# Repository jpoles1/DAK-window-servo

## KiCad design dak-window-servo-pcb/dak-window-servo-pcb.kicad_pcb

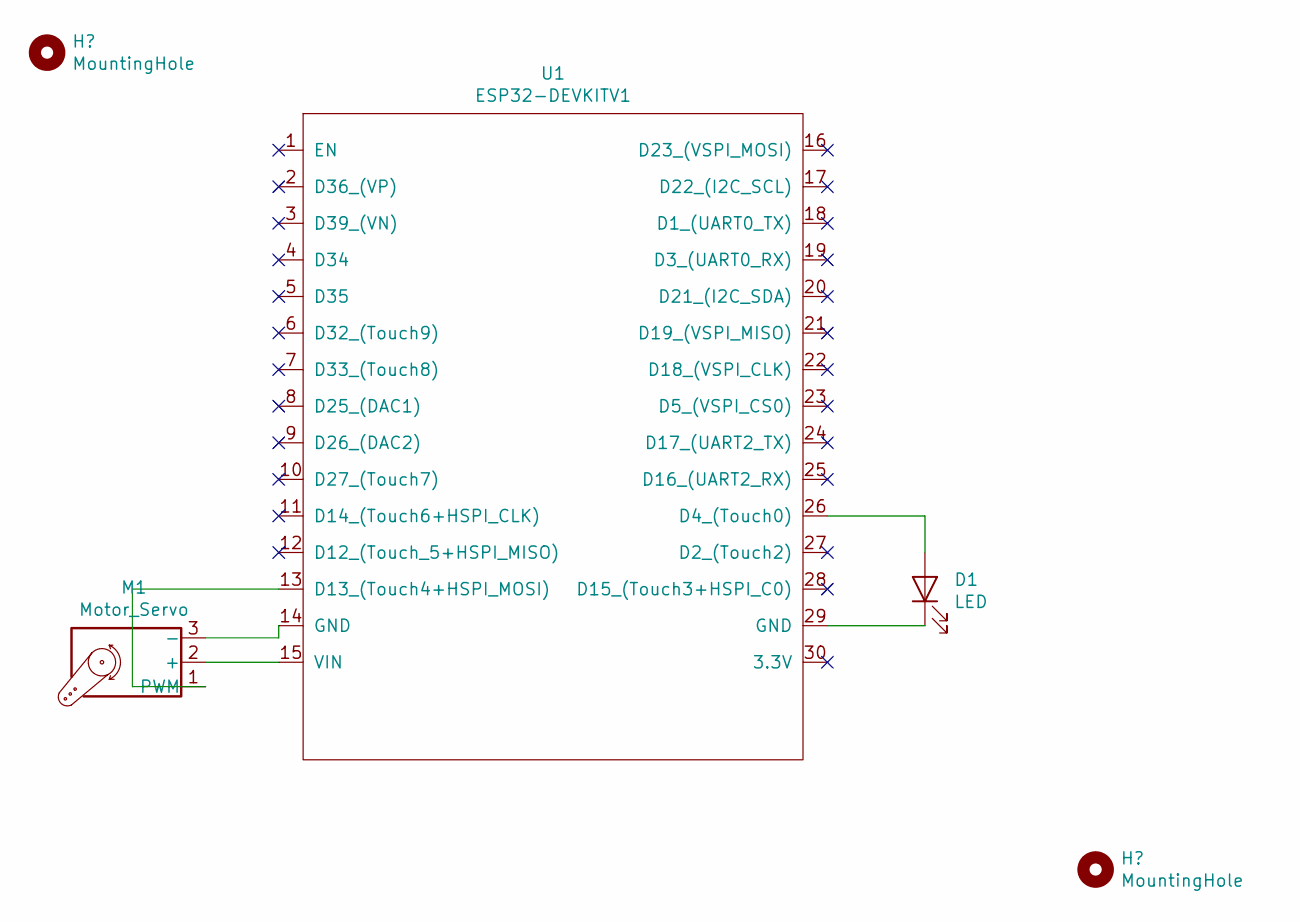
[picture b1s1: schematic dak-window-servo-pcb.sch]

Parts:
D1: LED; LED_D3.0mm
M1: Motor_Servo; Servo-Header
U1: ESP32-DEVKITV1

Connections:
unnamed: D1.1 (K), U1.29 (GND)
unnamed: D1.2 (A), U1.26 (D4_(Touch0))
unnamed: M1.1 (PWM), U1.13 (D13_(Touch4+HSPI_MOSI))
unnamed: M1.2 (+), U1.15 (VIN)
unnamed: M1.3 (-), U1.14 (GND)

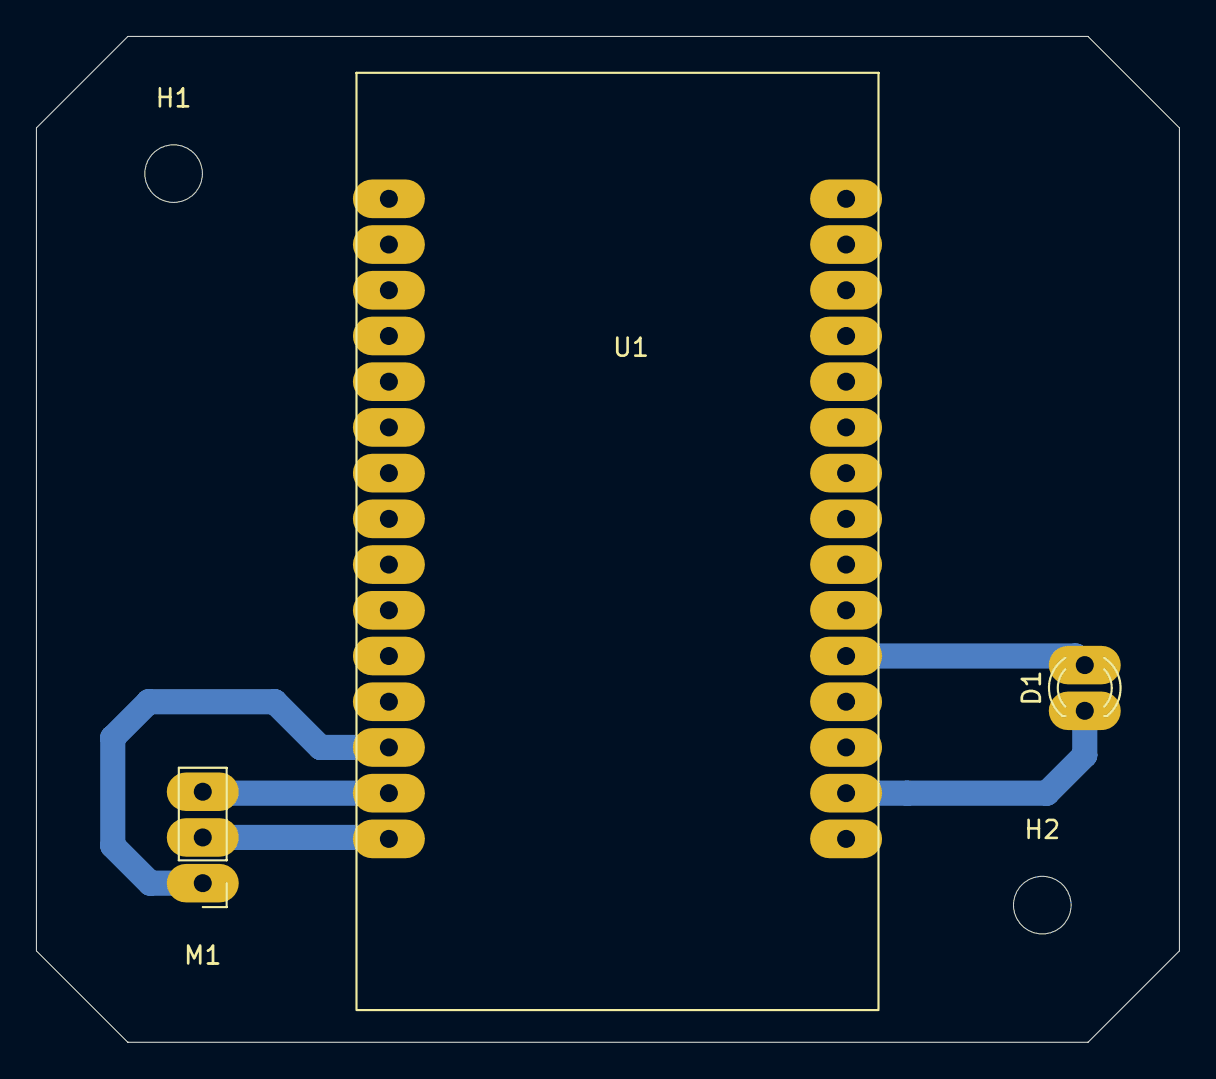
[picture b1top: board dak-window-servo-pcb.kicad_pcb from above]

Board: 2 copper layers, 63.5 x 55.9 mm, 5 parts (0 on the bottom side), 5 nets.

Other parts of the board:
H1, H2: MountingHole; MountingHole_3.2mm_M3

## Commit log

2019-07-31 wpa enterprise
2019-10-20 gitignore
2019-10-21 Ping/pong functionality!
2019-11-03 Getting ready for switch to esp32
2019-11-03 ESP32 servo working!
